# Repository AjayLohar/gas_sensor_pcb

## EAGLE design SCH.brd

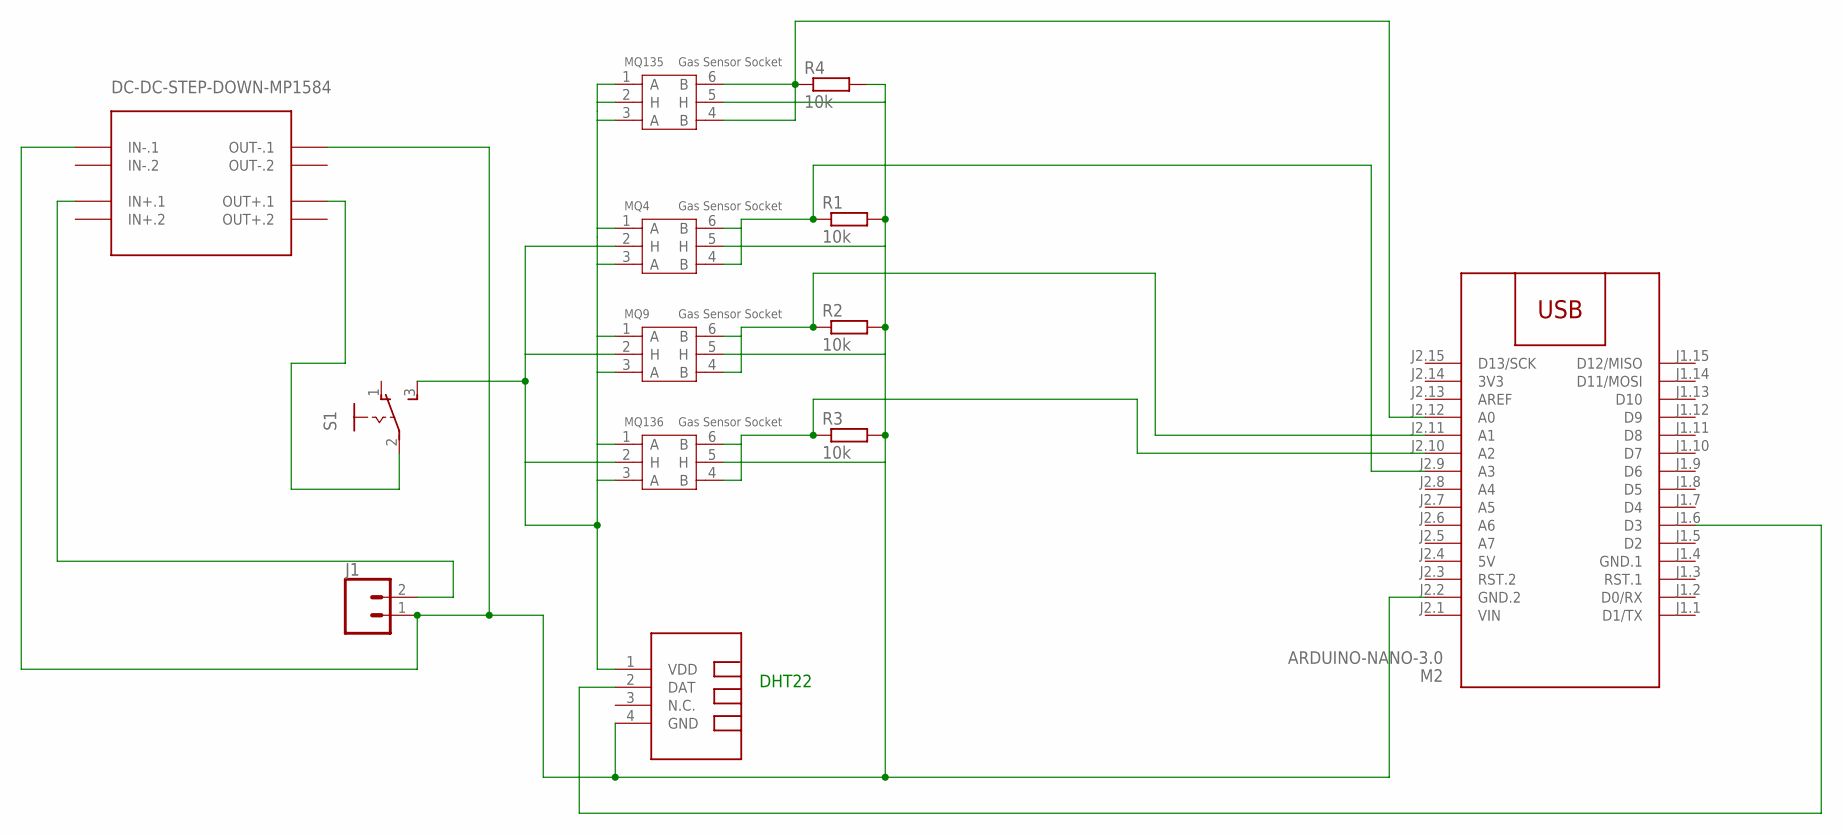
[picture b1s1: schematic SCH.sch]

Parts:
J1: CONN_021X02_NO_SILK; 1X02_NO_SILK
M2: ARDUINO-NANO-3.0
MQ4, MQ9, MQ135, MQ136: Gas Sensor Socket; 6P-D17.6X9.8H
R1, R2, R3, R4: 10k; 0204/7
S1: 255SB
U$1: TEMP-HUM-SENSOR-DHT22
U$2: DC-DC-STEP-DOWN-MP1584

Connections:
3V3: M2.J2.14 (3V3)
5V: M2.J2.4 (5V)
GND.1: M2.J1.4 (GND.1)
unnamed: M2.J2.9 (A3), MQ4.4 (B), MQ4.6 (B), R1.1
unnamed: M2.J2.11 (A1), MQ9.4 (B), MQ9.6 (B), R2.1
unnamed: M2.J2.10 (A2), MQ136.4 (B), MQ136.6 (B), R3.1
unnamed: J1.1, M2.J2.2 (GND.2), MQ4.5 (H), MQ9.5 (H), MQ135.5 (H), MQ136.5 (H), R1.2, R2.2, R3.2, R4.2, U$1.4 (GND), U$2.IN-.1, U$2.OUT-.1
unnamed: MQ4.1 (A), MQ4.2 (H), MQ4.3 (A), MQ9.1 (A), MQ9.2 (H), MQ9.3 (A), MQ135.1 (A), MQ135.2 (H), MQ135.3 (A), MQ136.1 (A), MQ136.2 (H), MQ136.3 (A), S1.3 (S), U$1.1 (VDD)
unnamed: J1.2, U$2.IN+.1
unnamed: M2.J2.12 (A0), MQ135.4 (B), MQ135.6 (B), R4.1
unnamed: S1.2, U$2.OUT+.1
unnamed: M2.J1.6 (D3), U$1.2 (DAT)
VIN: M2.J2.1 (VIN)

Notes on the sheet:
DHT22

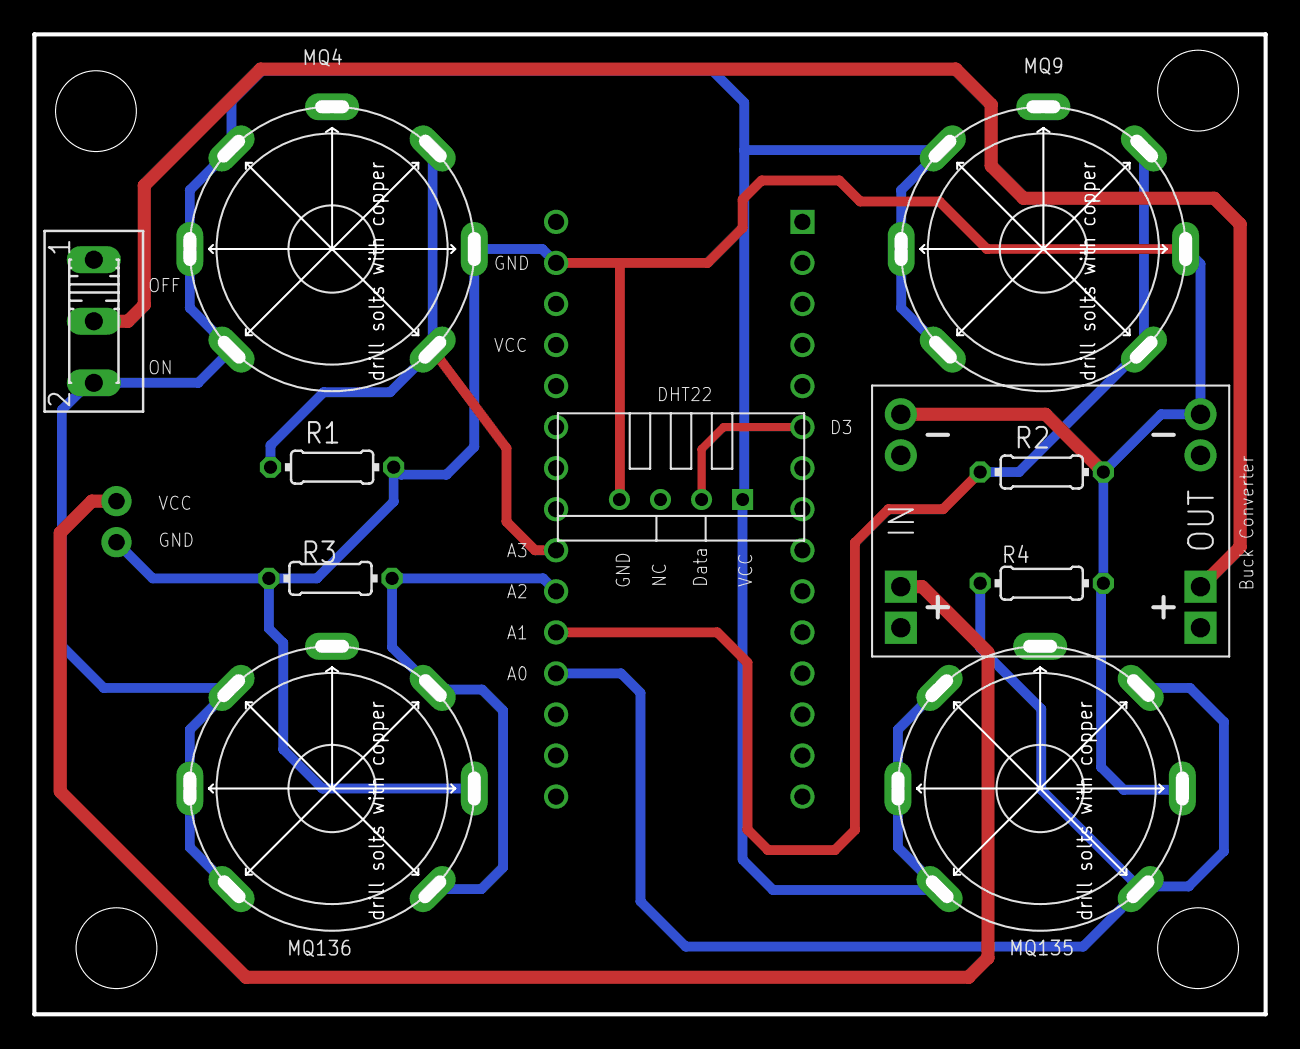
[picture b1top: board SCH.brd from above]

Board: 2 copper layers, 75.6 x 60.1 mm, 13 parts (1 on the bottom side), 9 nets.

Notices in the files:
parts and their libraries:
diy-modules: Released under the Creative Commons Attribution 4.0 International License: http://creativecommons.org/licenses/by/4.0
SparkFun-Connectors: Licensing: Creative Commons ShareAlike 4.0 International - https://creativecommons.org/licenses/by-sa/4.0
